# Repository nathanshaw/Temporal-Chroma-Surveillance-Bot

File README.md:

# Temporal-Chroma-Surveillance-Bot
The Temporal Chroma Surveilance Bot and the '6 x 9 = 42' installation.

Processing Dependancies:
--------------
video (library)
simpletweet (library)

Raspberry Pi Dependancies:
--------------
GL Video (libray)
simpletweet (library)

Controls
-------------
r = show red map
g = show green map
b = show blue map
n = new maps
m = go to new map mode
c = flip color separation
= = increase frame rate
- = decrease frame rate

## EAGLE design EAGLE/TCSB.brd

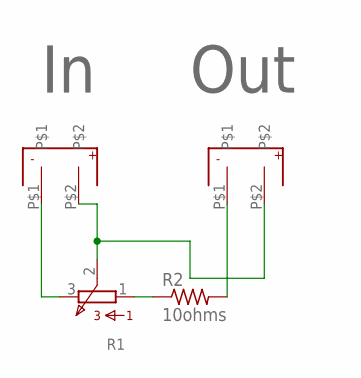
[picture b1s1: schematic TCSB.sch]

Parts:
R1: 308/309; 308
R2: 10ohms; 0204/7
U$1, U$2: RCA-YELLOW

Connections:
unnamed: R2.2, U$2.P$1
unnamed: R1.2, U$1.P$2, U$2.P$2
unnamed: R1.3, U$1.P$1
unnamed: R1.1, R2.1

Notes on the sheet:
Out

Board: 2 copper layers, 4 parts (0 on the bottom side), 4 nets, no tracks yet.

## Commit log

2017-03-16 added eagle files
2017-04-22 added board and firmware for two versions
2017-04-22 updated gitignore
2017-04-26 updated code for the one button version
2017-04-26 updated ctsb
2017-04-26 got interface working with the program
2017-04-29 updated slit-scan to have 12 differnet modes now
2017-06-10 added new picture to readme
2017-09-02 minor changes:
2019-08-23 made a new folder for the raspberry pi version of the script
2019-08-23 moved repeated masks to a masks folder on the top level, modified the rpi-no twitter version
